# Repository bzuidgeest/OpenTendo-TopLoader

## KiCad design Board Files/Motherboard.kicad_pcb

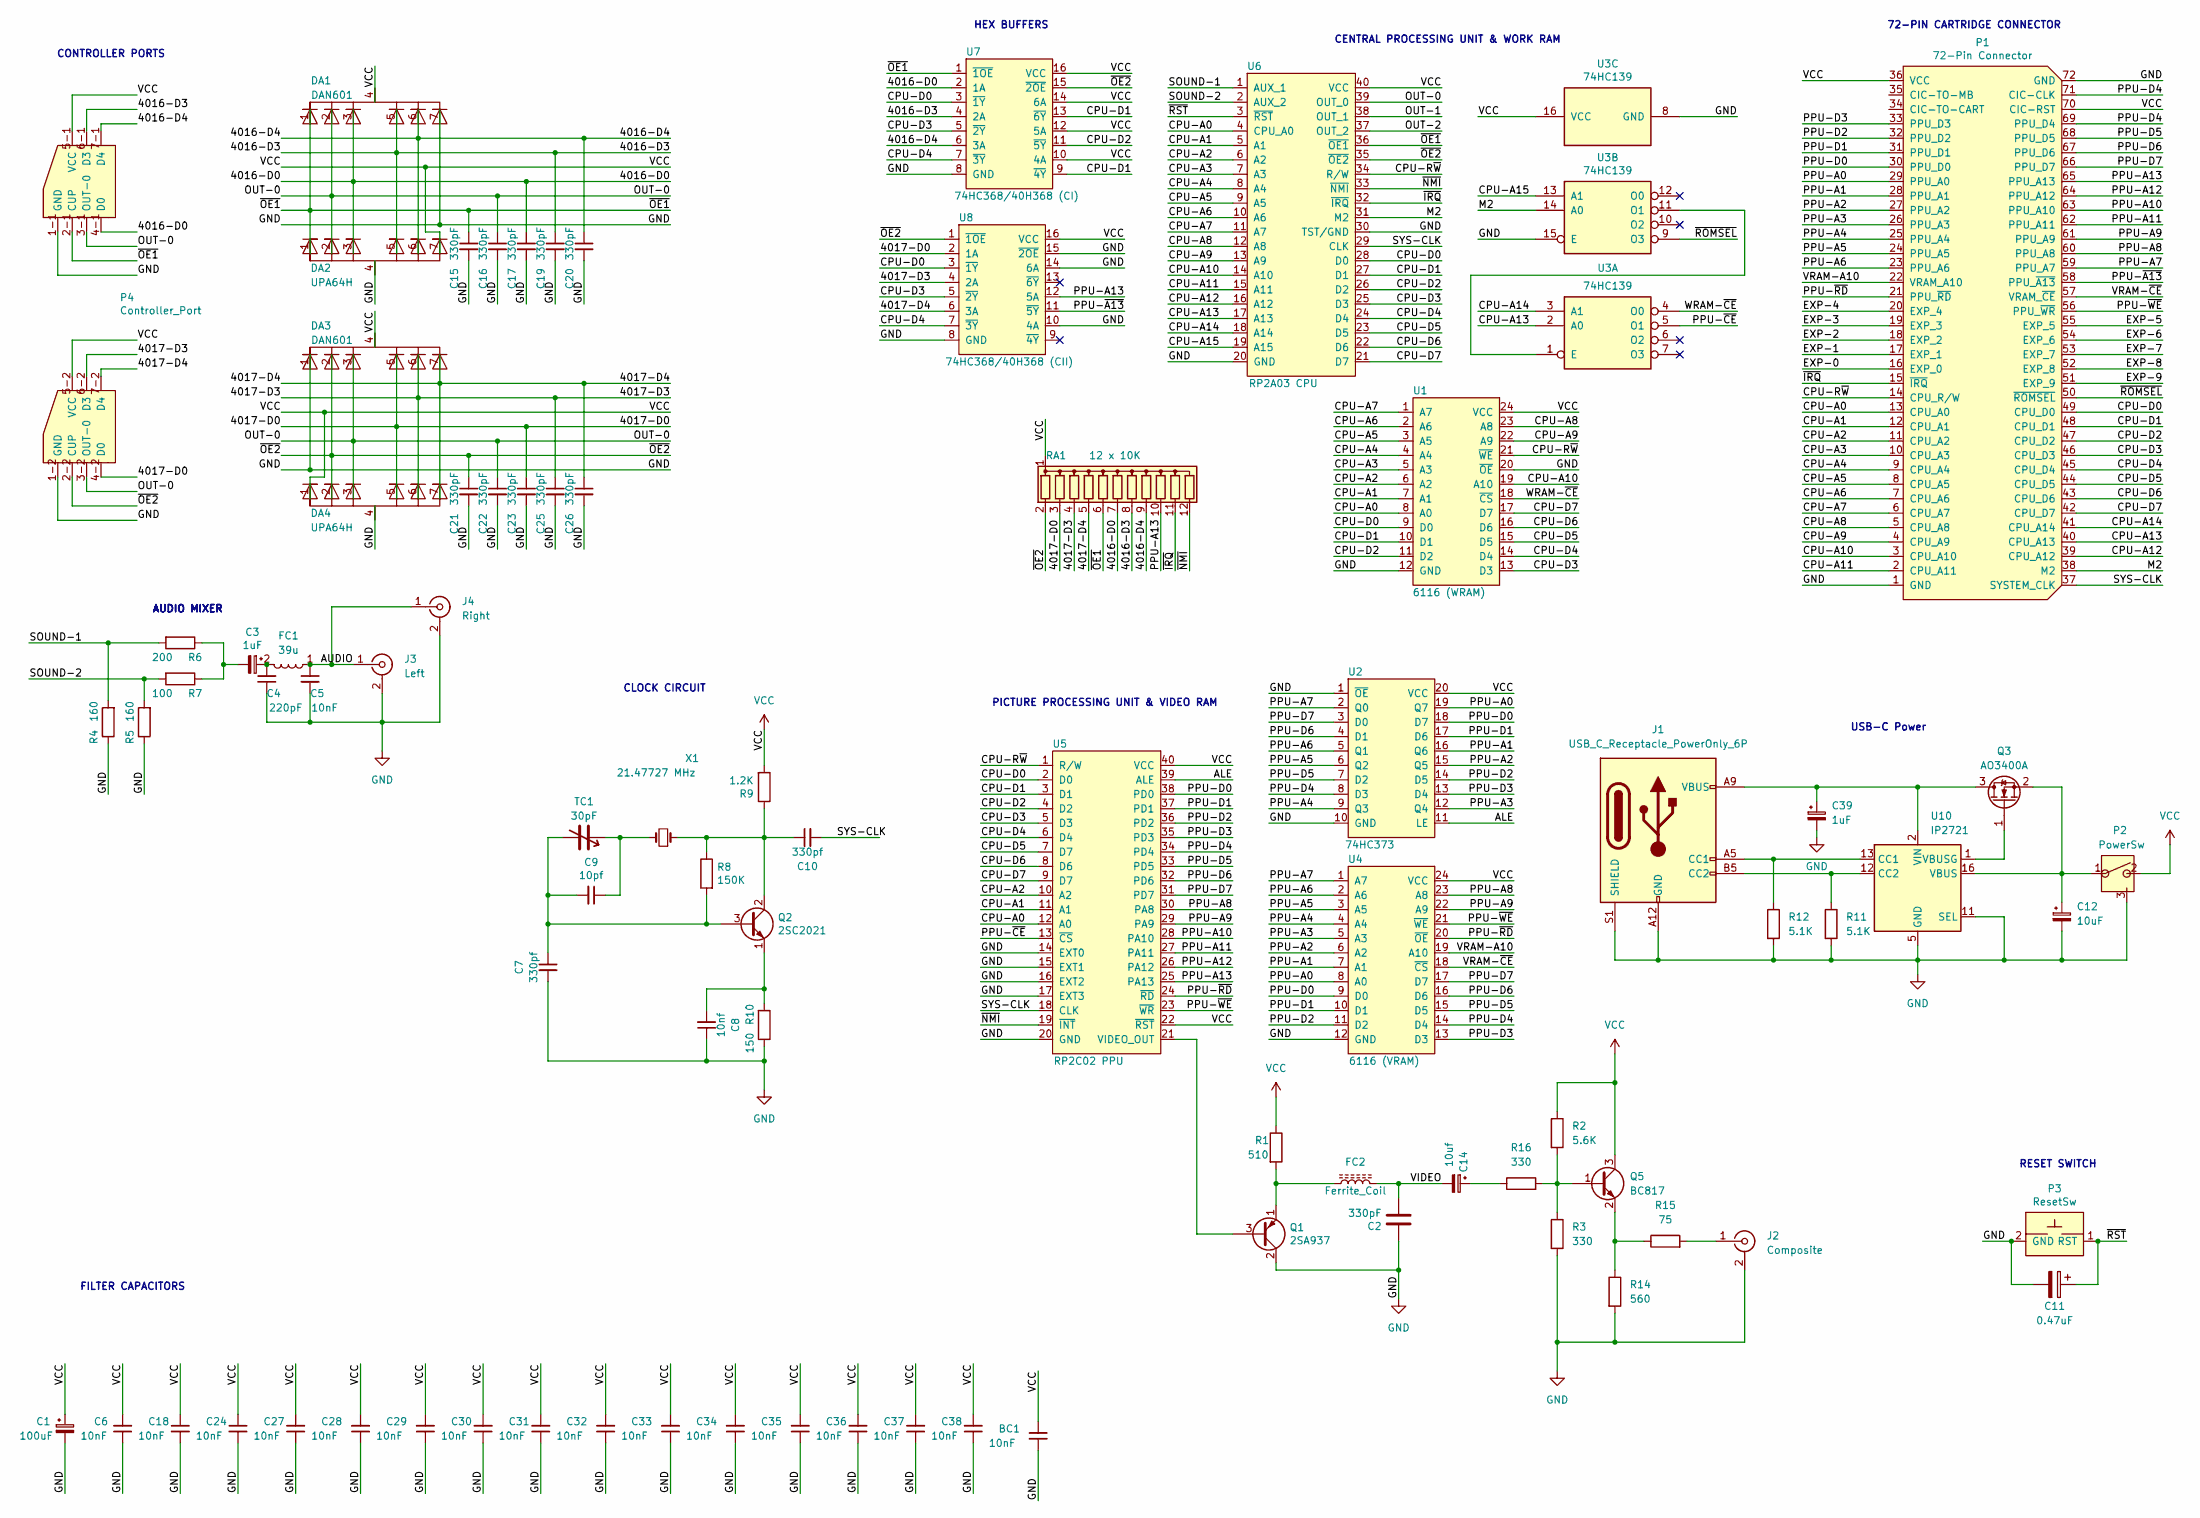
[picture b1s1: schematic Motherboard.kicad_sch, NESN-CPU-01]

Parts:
BC1: 10nF; C_Disc_D6.0mm_W2.5mm_P5.00mm
C1: 100uF; CP_Radial_D5.0mm_P2.50mm
C2: 330pF; C_Disc_D3.0mm_W2.0mm_P2.50mm
C3: 1uF; CP_Radial_D5.0mm_P2.50mm
C4: 220pF; C_Disc_D3.0mm_W1.6mm_P2.50mm
C5, C6: 10nF; C_Disc_D5.0mm_W2.5mm_P5.00mm
C7, C10: 330pf; C_Disc_D3.0mm_W1.6mm_P2.50mm
C8: 10nf; C_Disc_D3.0mm_W2.0mm_P2.50mm
C9: 10pf; C_Disc_D3.0mm_W2.0mm_P2.50mm
C11: 0.47uF; CP_Radial_D5.0mm_P2.50mm
C12: 10uF; CP_Radial_D6.3mm_P2.50mm
C14: 10uf; CP_Radial_D5.0mm_P2.50mm
C15, C16, C17, C19, C20, C21, C22, C23, C25, C26: 330pF; C_Disc_D3.0mm_W1.6mm_P2.50mm
C18, C24, C28, C30, C31, C36, C37, C38: 10nF; C_Disc_D3.0mm_W1.6mm_P2.50mm
C27, C29, C32, C33, C34, C35: 10nF; C_Disc_D3.0mm_W2.0mm_P2.50mm
C39: 1uF; CP_Radial_D6.3mm_P2.50mm
DA1, DA3: DAN601; R_Array_SIP7
DA2, DA4: UPA64H; R_Array_SIP7
FC1: 39u; R_Axial_DIN0207_L6.3mm_D2.5mm_P10.16mm_Horizontal
FC2: Ferrite_Coil; R_Axial_DIN0207_L6.3mm_D2.5mm_P10.16mm_Horizontal
J1: USB_C_Receptacle_PowerOnly_6P; USB_C_Receptacle_GCT_USB4125-xx-x-0190_6P_TopMnt_Horizontal
J2: Composite; PJRAN1X1U03AUX
J3: Left; PJRAN1X1U03AUX
J4: Right; PJRAN1X1U03AUX
P1: 72-Pin Connector; Cart Connector
P2: PowerSw; PowerSwitch
P3: ResetSw; ResetSwitch
P4: Controller_Port; Controller Ports
Q1: 2SA937; TO-126-3_Vertical
Q2: 2SC2021; TO-126-3_Vertical
Q3: AO3400A; SOT-23
Q5: BC817; SOT-23
R1: 510; R_Axial_DIN0207_L6.3mm_D2.5mm_P10.16mm_Horizontal
R2: 5.6K; R_Axial_DIN0207_L6.3mm_D2.5mm_P10.16mm_Horizontal
R3, R16: 330; R_Axial_DIN0207_L6.3mm_D2.5mm_P10.16mm_Horizontal
R4, R5: 160; R_Axial_DIN0207_L6.3mm_D2.5mm_P10.16mm_Horizontal
R6: 200; R_Axial_DIN0207_L6.3mm_D2.5mm_P10.16mm_Horizontal
R7: 100; R_Axial_DIN0207_L6.3mm_D2.5mm_P10.16mm_Horizontal
R8: 150K; R_Axial_DIN0207_L6.3mm_D2.5mm_P10.16mm_Horizontal
R9: 1.2K; R_Axial_DIN0207_L6.3mm_D2.5mm_P10.16mm_Horizontal
R10: 150; R_Axial_DIN0207_L6.3mm_D2.5mm_P10.16mm_Horizontal
R11, R12: 5.1K; R_Axial_DIN0207_L6.3mm_D2.5mm_P10.16mm_Horizontal
R14: 560; R_Axial_DIN0207_L6.3mm_D2.5mm_P10.16mm_Horizontal
R15: 75; R_Axial_DIN0207_L6.3mm_D2.5mm_P10.16mm_Horizontal
RA1: 12 x 10K; R_Array_SIP12
TC1: 30pF; TrimmerCap-THT
U1: 6116 (WRAM); DIP-24_W7.62mm
U2: 74HC373; DIP-20_W7.62mm
U3: 74HC139; DIP-16_W7.62mm
U4: 6116 (VRAM); DIP-24_W7.62mm
U5: RP2C02 PPU; DIP-40_W15.24mm
U6: RP2A03 CPU; DIP-40_W15.24mm
U7: 74HC368/40H368 (CI); DIP-16_W7.62mm
U8: 74HC368/40H368 (CII); DIP-16_W7.62mm
U10: IP2721; TSSOP-16_4.4x5mm_P0.65mm
X1: 21.47727 MHz; Crystal_HC49-U_Vertical

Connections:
/4016-D0: C17.1, DA1.3, DA2.3, P4.4-1 (D0), RA1.7 (R6), U7.2 (1A)
/4016-D3: C19.1, DA1.5, DA2.5, P4.6-1 (D3), RA1.8 (R7), U7.4 (2A)
/4016-D4: C20.1, DA1.6, DA2.6, P4.7-1 (D4), RA1.9 (R8), U7.6 (3A)
/4017-D0: C23.1, DA3.5, DA4.5, P4.4-2 (D0), RA1.3 (R2), U8.2 (1A)
/4017-D3: C25.1, DA3.6, DA4.6, P4.6-2 (D3), RA1.4 (R3), U8.4 (2A)
/4017-D4: C26.1, DA3.7, DA4.7, P4.7-2 (D4), RA1.5 (R4), U8.6 (3A)
/ALE: U2.11 (LE), U5.39 (ALE)
/AUDIO: C5.1, FC1.1, J3.1 (In), J4.1 (In)
/CPU-A0: P1.13 (CPU_A0), U1.8 (A0), U5.12 (A0), U6.4 (CPU_A0)
/CPU-A1: P1.12 (CPU_A1), U1.7 (A1), U5.11 (A1), U6.5 (A1)
/CPU-A2: P1.11 (CPU_A2), U1.6 (A2), U5.10 (A2), U6.6 (A2)
/CPU-A3: P1.10 (CPU_A3), U1.5 (A3~), U6.7 (A3)
/CPU-A4: P1.9 (CPU_A4), U1.4 (A4~), U6.8 (A4)
/CPU-A5: P1.8 (CPU_A5), U1.3 (A5~), U6.9 (A5)
/CPU-A6: P1.7 (CPU_A6), U1.2 (A6~), U6.10 (A6)
/CPU-A7: P1.6 (CPU_A7), U1.1 (A7), U6.11 (A7)
/CPU-A8: P1.5 (CPU_A8), U1.23 (A8), U6.12 (A8)
/CPU-A9: P1.4 (CPU_A9), U1.22 (A9), U6.13 (A9)
/CPU-A10: P1.3 (CPU_A10), U1.19 (A10), U6.14 (A10)
/CPU-A11: P1.2 (CPU_A11), U6.15 (A11)
/CPU-A12: P1.39 (CPU_A12), U6.16 (A12)
/CPU-A13: P1.40 (CPU_A13), U3.2 (A0), U6.17 (A13)
/CPU-A14: P1.41 (CPU_A14), U3.3 (A1), U6.18 (A14)
/CPU-A15: U3.13 (A1), U6.19 (A15)
/CPU-D0: P1.49 (CPU_D0), U1.9 (D0), U5.2 (D0), U6.28 (D0), U7.3 (~1Y), U8.3 (~1Y)
/CPU-D1: P1.48 (CPU_D1), U1.10 (D1), U5.3 (D1), U6.27 (D1), U7.9 (~4Y), U7.13 (~6Y)
/CPU-D2: P1.47 (CPU_D2), U1.11 (D2), U5.4 (D2), U6.26 (D2), U7.11 (~5Y)
/CPU-D3: P1.46 (CPU_D3), U1.13 (D3), U5.5 (D3), U6.25 (D3), U7.5 (~2Y), U8.5 (~2Y)
/CPU-D4: P1.45 (CPU_D4), U1.14 (D4), U5.6 (D4), U6.24 (D4), U7.7 (~3Y), U8.7 (~3Y)
/CPU-D5: P1.44 (CPU_D5), U1.15 (D5), U5.7 (D7), U6.23 (D5)
/CPU-D6: P1.43 (CPU_D6), U1.16 (D6), U5.8 (D6), U6.22 (D6)
/CPU-D7: P1.42 (CPU_D7), U1.17 (D7), U5.9 (D7), U6.21 (D7)
/CPU-R~W: P1.14 (CPU_R/W), U1.21 (~WE), U5.1 (R/W), U6.34 (R/W)
/EXP-0: P1.16 (EXP_0)
/EXP-1: P1.17 (EXP_1)
/EXP-4: P1.20 (EXP_4)
/EXP-7: P1.53 (EXP_7)
/EXP-8: P1.52 (EXP_8)
/EXP-9: P1.51 (EXP_9)
/M2: P1.38 (M2), U3.14 (A0), U6.31 (M2)
/OUT-0: C16.1, C22.1, DA1.2, DA2.2, DA3.3, DA4.3, P4.3-1 (OUT-0), P4.3-2 (OUT-0), U6.39 (OUT_0)
/OUT-1: U6.38 (OUT_1)
/OUT-2: U6.37 (OUT_2)
/PPU-A0: P1.29 (PPU_A0), U2.19 (Q7), U4.8 (A0)
/PPU-A1: P1.28 (PPU_A1), U2.16 (Q6), U4.7 (A1)
/PPU-A2: P1.27 (PPU_A2), U2.15 (Q5), U4.6 (A2)
/PPU-A3: P1.26 (PPU_A3), U2.12 (Q4), U4.5 (A3~)
/PPU-A4: P1.25 (PPU_A4), U2.9 (Q3), U4.4 (A4~)
/PPU-A5: P1.24 (PPU_A5), U2.6 (Q2), U4.3 (A5~)
/PPU-A6: P1.23 (PPU_A6), U2.5 (Q1), U4.2 (A6~)
/PPU-A7: P1.59 (PPU_A7), U2.2 (Q0), U4.1 (A7)
/PPU-A8: P1.60 (PPU_A8), U4.23 (A8), U5.30 (PA8)
/PPU-A9: P1.61 (PPU_A9), U4.22 (A9), U5.29 (PA9)
/PPU-A10: P1.63 (PPU_A10), U5.28 (PA10)
/PPU-A11: P1.62 (PPU_A11), U5.27 (PA11)
/PPU-A12: P1.64 (PPU_A12), U5.26 (PA12)
/PPU-A13: P1.65 (PPU_A13), RA1.10 (R9), U5.25 (PA13), U8.12 (5A)
/PPU-D0: P1.30 (PPU_D0), U2.18 (D7), U4.9 (D0), U5.38 (PD0)
/PPU-D1: P1.31 (PPU_D1), U2.17 (D6), U4.10 (D1), U5.37 (PD1)
/PPU-D2: P1.32 (PPU_D2), U2.14 (D5), U4.11 (D2), U5.36 (PD2)
/PPU-D3: P1.33 (PPU_D3), U2.13 (D4), U4.13 (D3), U5.35 (PD3)
/PPU-D4: P1.69 (PPU_D4), P1.71 (CIC-CLK), U2.8 (D3), U4.14 (D4), U5.34 (PD4)
/PPU-D5: P1.68 (PPU_D5), U2.7 (D2), U4.15 (D5), U5.33 (PD5)
/PPU-D6: P1.67 (PPU_D6), U2.4 (D1), U4.16 (D6), U5.32 (PD6)
/PPU-D7: P1.66 (PPU_D7), U2.3 (D0), U4.17 (D7), U5.31 (PD7)
/PPU-~A13: P1.58 (PPU_~A13), U8.11 (~5Y)
/PPU-~CE: U3.5 (O1), U5.13 (~CS)
/PPU-~RD: P1.21 (PPU_~RD), U4.20 (~OE), U5.24 (~RD)
/PPU-~WE: P1.56 (PPU_~WR), U4.21 (~WE), U5.23 (~WR)
/SOUND-1: R4.2, R6.2, U6.1 (AUX_1)
/SOUND-2: R5.2, R7.2, U6.2 (AUX_2)
/SYS-CLK: C10.2, P1.37 (SYSTEM_CLK), U5.18 (CLK), U6.29 (CLK)
/VIDEO: C2.2, C14.2, FC2.2
/VRAM-A10: P1.22 (VRAM_A10), U4.19 (A10)
/VRAM-~CE: P1.57 (VRAM_~CE), U4.18 (~CS)
/WRAM-~CE: U1.18 (~CS), U3.4 (O0)
/~IRQ: P1.15 (~IRQ), RA1.11 (R10), U6.32 (~IRQ)
/~NMI: RA1.12 (R11), U5.19 (~INT), U6.33 (~NMI)
/~OE1: C15.1, DA1.1, DA2.1, P4.2-1 (CUP), RA1.6 (R5), U6.36 (~OE1), U7.1 (~1OE)
/~OE2: C21.1, DA3.2, DA4.2, P4.2-2 (CUP), RA1.2 (R1), U6.35 (~OE2), U7.15 (~2OE), U8.1 (~1OE)
/~ROMSEL: P1.50 (~ROMSEL), U3.9 (O3)
/~RST: C11.1, P3.1 (RST), U6.3 (~RST)
GND: BC1.1, C1.2, C2.1, C4.1, C5.2, C6.1, C7.2, C8.1, C11.2, C12.2, C15.2, C16.2, C17.2, C18.2, C19.2, C20.2, C21.2, C22.2, C23.2, C24.2, C25.2, C26.2, C27.1, C28.1, C29.1, C30.1, C31.1, C32.1, C33.1, C34.1, C35.1, C36.1, C37.1, C38.1, C39.2, DA1.7, DA2.4, DA3.1, DA4.4, J1.A12 (GND), J1.B12 (GND), J1.S1 (SHIELD), J2.2 (Ext), J3.2 (Ext), J4.2 (Ext), P1.1 (GND), P1.72 (GND), P2.3, P3.2 (GND), P4.1-1 (GND), P4.1-2 (GND), Q1.2 (C), R3.2, R4.1, R5.1, R10.1, R11.2, R12.2, R14.2, U1.12 (GND~), U1.20 (~OE), U2.1 (~OE), U2.10 (GND), U3.8 (GND), U3.15 (E), U4.12 (GND~), U5.14 (EXT0), U5.15 (EXT1), U5.16 (EXT2), U5.17 (EXT3), U5.20 (GND), U6.20 (GND), U6.30 (TST/GND), U7.8 (GND), U8.8 (GND), U8.10 (4A), U8.14 (6A), U8.15 (~2OE), U10.5 (GND), U10.11 (SEL)
unnamed: C3.1, C4.2, FC1.2
unnamed: C3.2, R6.1, R7.1
unnamed: C9.1, TC1.1, X1.2
unnamed: C14.1, R16.1
unnamed: J1.A5 (CC1), R12.1, U10.13 (CC1)
unnamed: J1.B5 (CC2), R11.1, U10.12 (CC2)
unnamed: J2.1 (In), R15.2
unnamed: Q1.3 (B), U5.21 (VIDEO_OUT)
unnamed: FC2.1, Q1.1 (E), R1.2
unnamed: C7.1, C9.2, Q2.3 (B), R8.2, TC1.2
unnamed: C10.1, Q2.2 (C), R8.1, R9.1, X1.1
unnamed: C8.2, Q2.1 (E), R10.2
unnamed: C39.1, J1.A9 (VBUS), J1.B9 (VBUS), Q3.3 (D), U10.2 (VIN)
unnamed: Q3.1 (G), U10.1 (VBUSG)
unnamed: C12.1, P2.1, Q3.2 (S), U10.16 (VBUS)
unnamed: Q5.1 (B), R2.2, R3.1, R16.2
unnamed: Q5.2 (E), R14.1, R15.1
unnamed: U3.1 (E), U3.11 (O1)
VCC: BC1.2, C1.1, C6.2, C18.1, C24.1, C27.2, C28.2, C29.2, C30.2, C31.2, C32.2, C33.2, C34.2, C35.2, C36.2, C37.2, C38.2, DA1.4, DA2.7, DA3.4, DA4.1, P1.36 (VCC), P1.70 (CIC-RST), P2.2, P4.5-1 (VCC), P4.5-2 (VCC), Q5.3 (C), R1.1, R2.1, R9.2, RA1.1 (common), U1.24 (VCC), U2.20 (VCC), U3.16 (VCC), U4.24 (VCC), U5.22 (~RST), U5.40 (VCC), U6.40 (VCC), U7.10 (4A), U7.12 (5A), U7.14 (6A), U7.16 (VCC), U8.16 (VCC)

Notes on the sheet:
AUDIO MIXER
CLOCK CIRCUIT
FILTER CAPACITORS
HEX BUFFERS
USB-C Power
PICTURE PROCESSING UNIT & VIDEO RAM
RESET SWITCH
CENTRAL PROCESSING UNIT & WORK RAM
CONTROLLER PORTS
72-PIN CARTRIDGE CONNECTOR

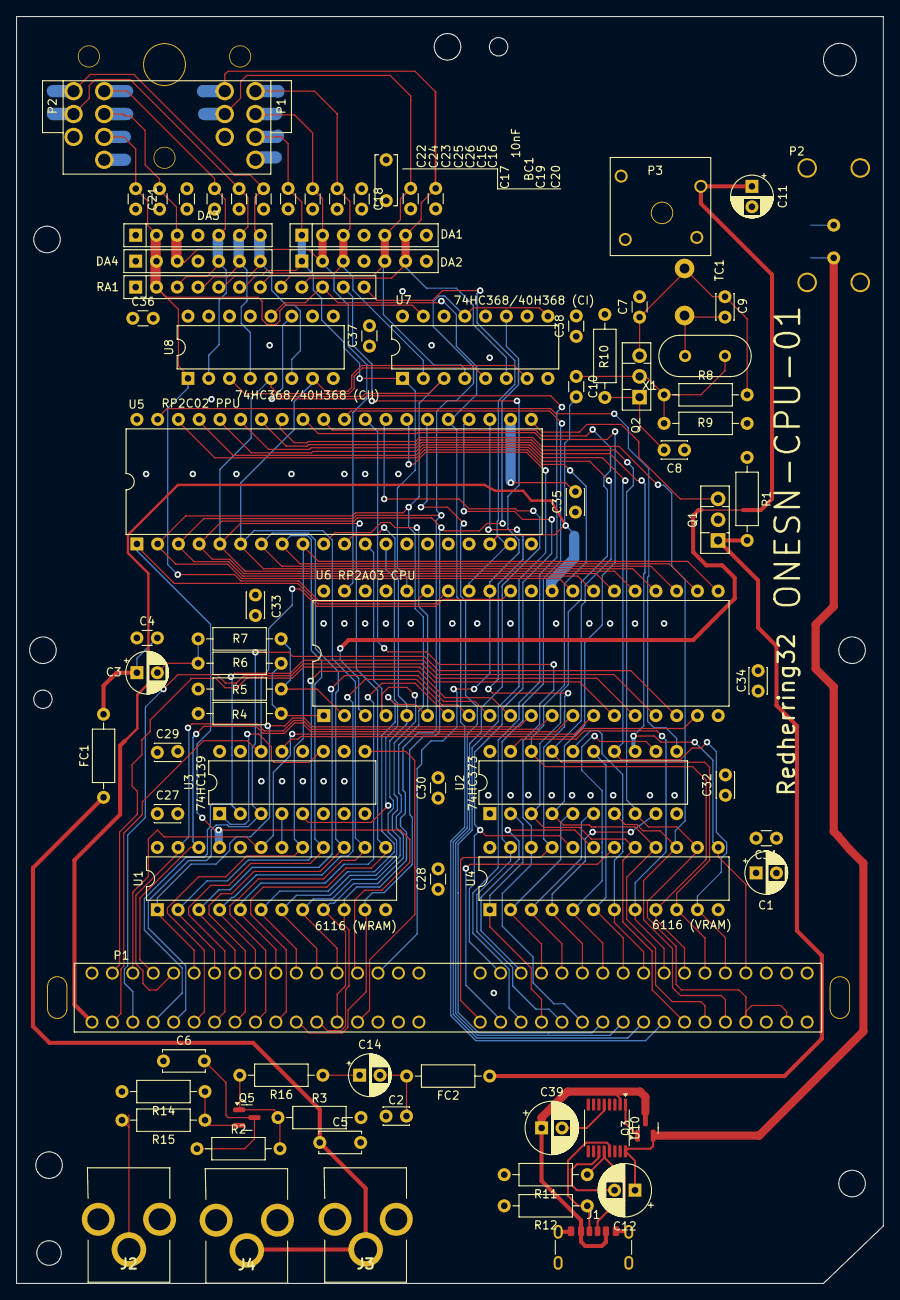
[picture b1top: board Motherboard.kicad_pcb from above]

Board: 4 copper layers, 106.1 x 155.0 mm, 84 parts (0 on the bottom side), 94 nets.

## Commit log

2024-05-12 first changes
2024-05-12 added start of usb C power supply
2024-05-13 Power supply complete?
2024-05-13 added video and audio
2024-05-17 little bit of routing
2024-06-16 Progress
2024-06-24 all connected up
2024-06-30 4 Layer complete
